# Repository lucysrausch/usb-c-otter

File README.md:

PCB based on the PD Buddy Sink by Clara Hobbs.

## License

PD Buddy Sink is Copyright (C) 2017 Clayton G. Hobbs, and made available under
the CERN Open Hardware Licence v1.2.  See LICENSE for more information.

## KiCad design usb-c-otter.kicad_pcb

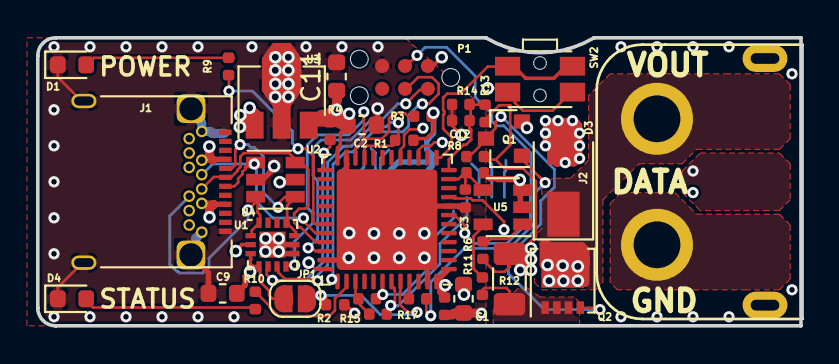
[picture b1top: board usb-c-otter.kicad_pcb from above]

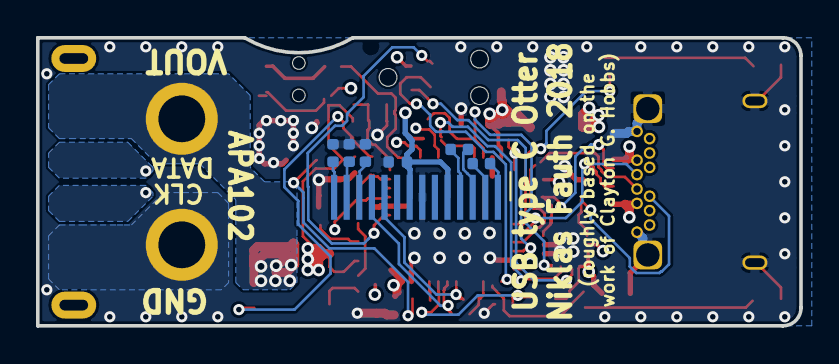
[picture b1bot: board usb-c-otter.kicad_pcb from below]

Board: 4 copper layers, 42.4 x 16.0 mm, 45 parts (7 on the bottom side), 38 nets.

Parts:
C1: 1.0μF 25V; C_0603_1608Metric
C2: 2.2μF; C_0603_1608Metric
C3, C4, C8, C12: 0.1μF; C_0402_1005Metric
C9, C11: 1μF; C_0603_1608Metric
C13, C14, C15, C16: 1uF; C_0402_1005Metric
D1: Power; LED_0603_1608Metric
D3: B140-E3; D_SMA
D4: Status; LED_0603_1608Metric
J1: 12401610E4-2A; USB_C_Receptacle_Amphenol_12401548E4-2A
J2: 5-20 V⎓; XT60_angle
J3: Conn_01x14; Harwin_M20-89014xx_1x14_P2.54mm_Horizontal
JP1: Boot; SolderJumper-2_P1.3mm_Open_RoundedPad1.0x1.5mm
P1: TC2030-CTX; TC2030-NL_SMALL
Q1: MMBT3904; SOT-23
Q2: DMP3017SFG; Diodes_PowerDI3333-8
R1, R3, R4, R7, R15, R17: 2kΩ; R_0402_1005Metric
R2: 10kΩ; R_0402_1005Metric
R5, R9, R10, R13, R14: 1k; R_0402_1005Metric
R6, R11: 15; R_0402_1005Metric
R8: 100kΩ; R_0402_1005Metric
R12: 10m; R_1206_3216Metric
R16: 560k; R_0402_1005Metric
SW2: Setup; SW_SPST_EVQP7C
U1: FUSB302BMPX; WQFN-14-1EP_2.5x2.5mm_P0.5mm_EP1.45x1.45mm
U2: STM32F072C8Ux; QFN-48-1EP_7x7mm_P0.5mm_EP5.6x5.6mm
U3: AP2204R-3.3; SOT-89-3
U4: USBLC6-2SC6; SOT-23-6
U5: Si8540; SOT-23-5

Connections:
+3V3: C2.1, C4.1, C8.1, C9.1, C11.1, J3.5, J3.8, JP1.1, P1.1, R1.2, R3.2, R4.2, SW2.1, U1.3, U1.4, U2.1, U2.9, U2.24, U2.36, U2.48, U3.3, U4.5
/BOOT: JP1.2, R2.2, U2.44
/OUT: D3.1, J2.1, Q2.5
/SETUP: SW2.2, U2.13
/STATUS: R10.1, U2.38
/SWCLK: P1.4, U2.37
/SWDIO: P1.2, U2.34
/nRST: P1.3, U2.7
CC1: J1.A5, U1.10, U1.11, U4.4
CC2: J1.B5, U1.1, U1.14, U4.3
GND: C1.2, C2.2, C3.2, C4.2, C8.2, C9.2, C11.2, C12.2, C14.2, C16.2, D1.1, D3.2, D4.1, J1.A1, J1.A12, J1.B1, J1.B12, J1.S1, J2.2, J3.7, P1.5, Q1.2, R2.1, R5.2, R14.2, R16.2, U1.8, U1.9, U1.15, U2.8, U2.23, U2.35, U2.47, U2.49, U3.2, U4.2, U5.2, U5.3
INT_N: R4.1, U1.5, U2.25
I_OUT: C3.1, R5.1, U2.11, U5.4
unnamed: C13.1, J3.3
unnamed: C13.2, J3.4
unnamed: C14.1, J3.13
unnamed: C15.1, J3.2
unnamed: C15.2, J3.1
unnamed: C16.1, J3.14
unnamed: D1.2, R9.2
unnamed: D4.2, R10.2
unnamed: J3.12, R16.1
unnamed: Q1.1, R7.2
unnamed: Q1.3, Q2.4, R8.2
unnamed: Q2.1, Q2.2, Q2.3, R11.2, R12.2
unnamed: R6.1, U5.1
unnamed: R9.1, U2.31
unnamed: R11.1, U5.5
OLED_PULLUP: R15.2, R17.2, U2.39
OLED_SCL: J3.10, R15.1, U2.42
OLED_SDA: J3.11, R17.1, U2.43
OUT_CTL: R7.1, U2.45
SCL: R1.1, U1.6, U2.21
SDA: R3.1, U1.7, U2.22
USB_DN: J1.A7, J1.B7, U2.32, U4.1
USB_DP: J1.A6, J1.B6, U2.33, U4.6
U_OUT: C12.1, R13.2, R14.1, U2.12
VBUS: C1.1, J1.A4, J1.A9, J1.B4, J1.B9, R6.2, R8.1, R12.1, R13.1, U1.2, U3.1
